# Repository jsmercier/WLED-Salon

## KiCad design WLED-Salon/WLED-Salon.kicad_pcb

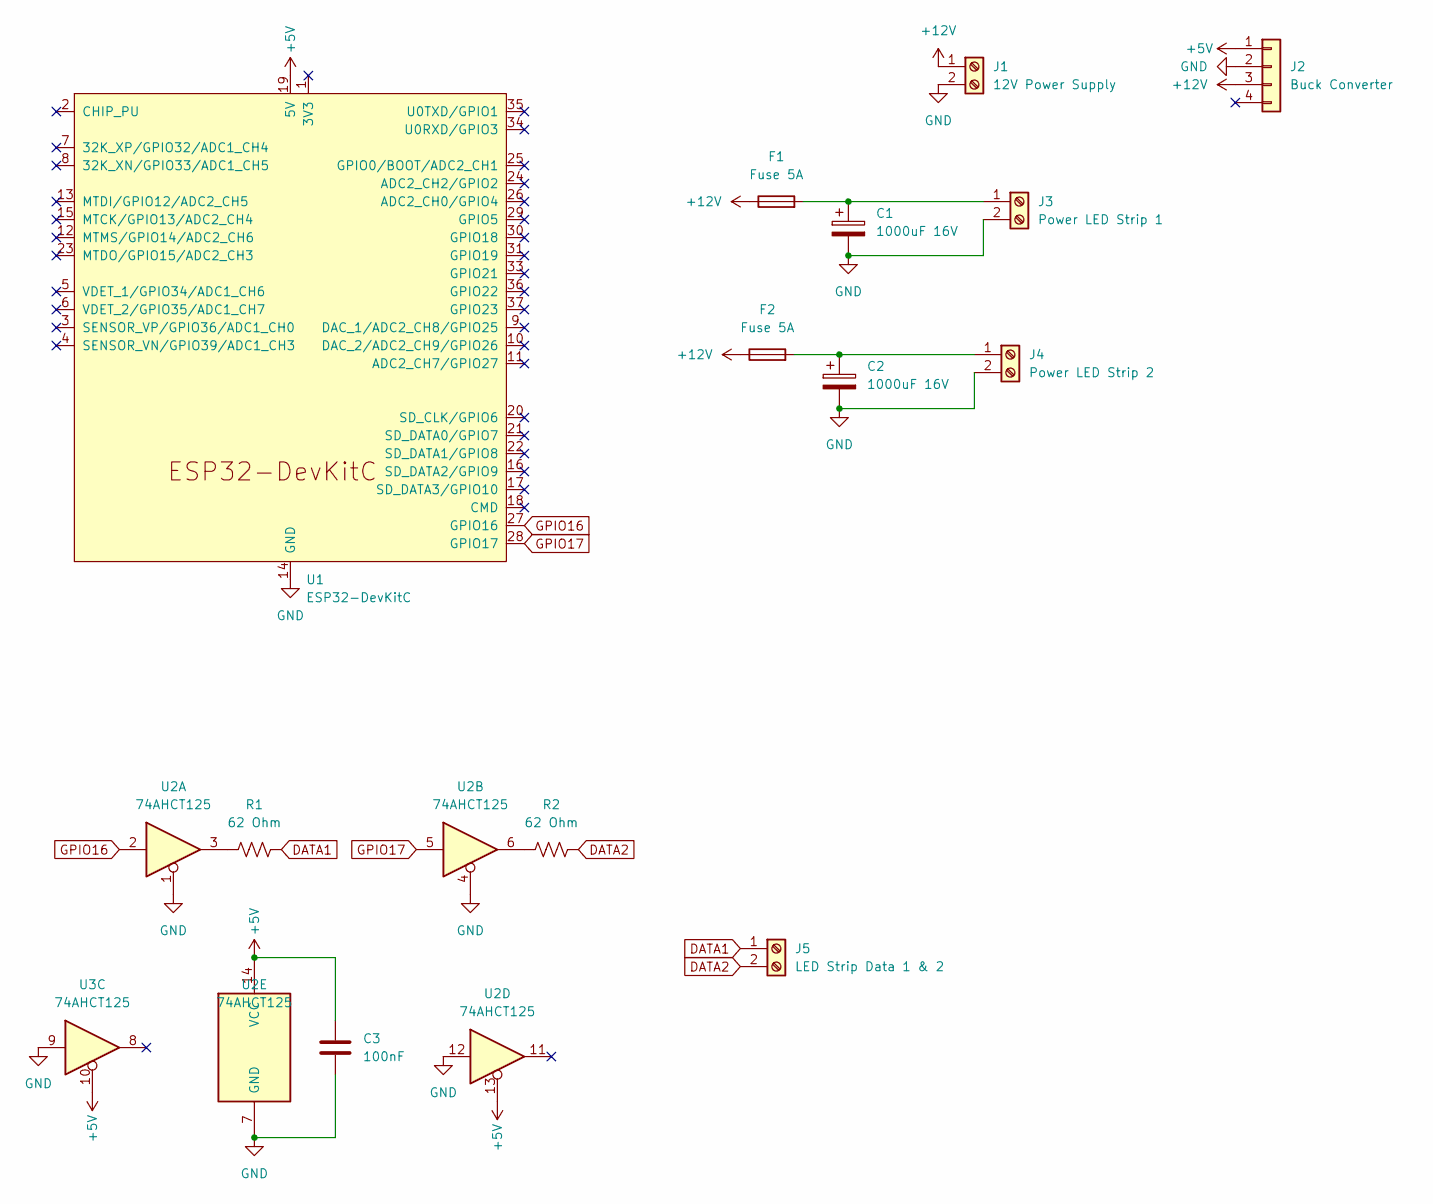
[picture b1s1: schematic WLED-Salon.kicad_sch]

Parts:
C1, C2: 1000uF 16V
C3: 100nF
F1, F2: Fuse 5A
J1: 12V Power Supply
J2: Buck Converter
J3: Power LED Strip 1
J4: Power LED Strip 2
J5: LED Strip Data 1 & 2
R1, R2: 62 Ohm
U1: ESP32-DevKitC
U2, U3: 74AHCT125; DIP-14_W7.62mm_Socket

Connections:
+5V: C3.1, J2.1, U1.19 (5V), U2.10, U2.13, U2.14 (VCC), U3.10
+12V: F1.1, F2.1, J1.1, J2.3
DATA1: J5.1, R1.2
DATA2: J5.2, R2.2
GND: C1.2, C2.2, C3.2, J1.2, J2.2, J3.2, J4.2, U1.14 (GND), U1.32 (GND), U1.38 (GND), U2.1, U2.4, U2.7 (GND), U2.9, U2.12, U3.9
GPIO16: U1.27 (GPIO16), U2.2
GPIO17: U1.28 (GPIO17), U2.5
unnamed: C1.1, F1.2, J3.1
unnamed: C2.1, F2.2, J4.1
unnamed: R1.1, U2.3
unnamed: R2.1, U2.6

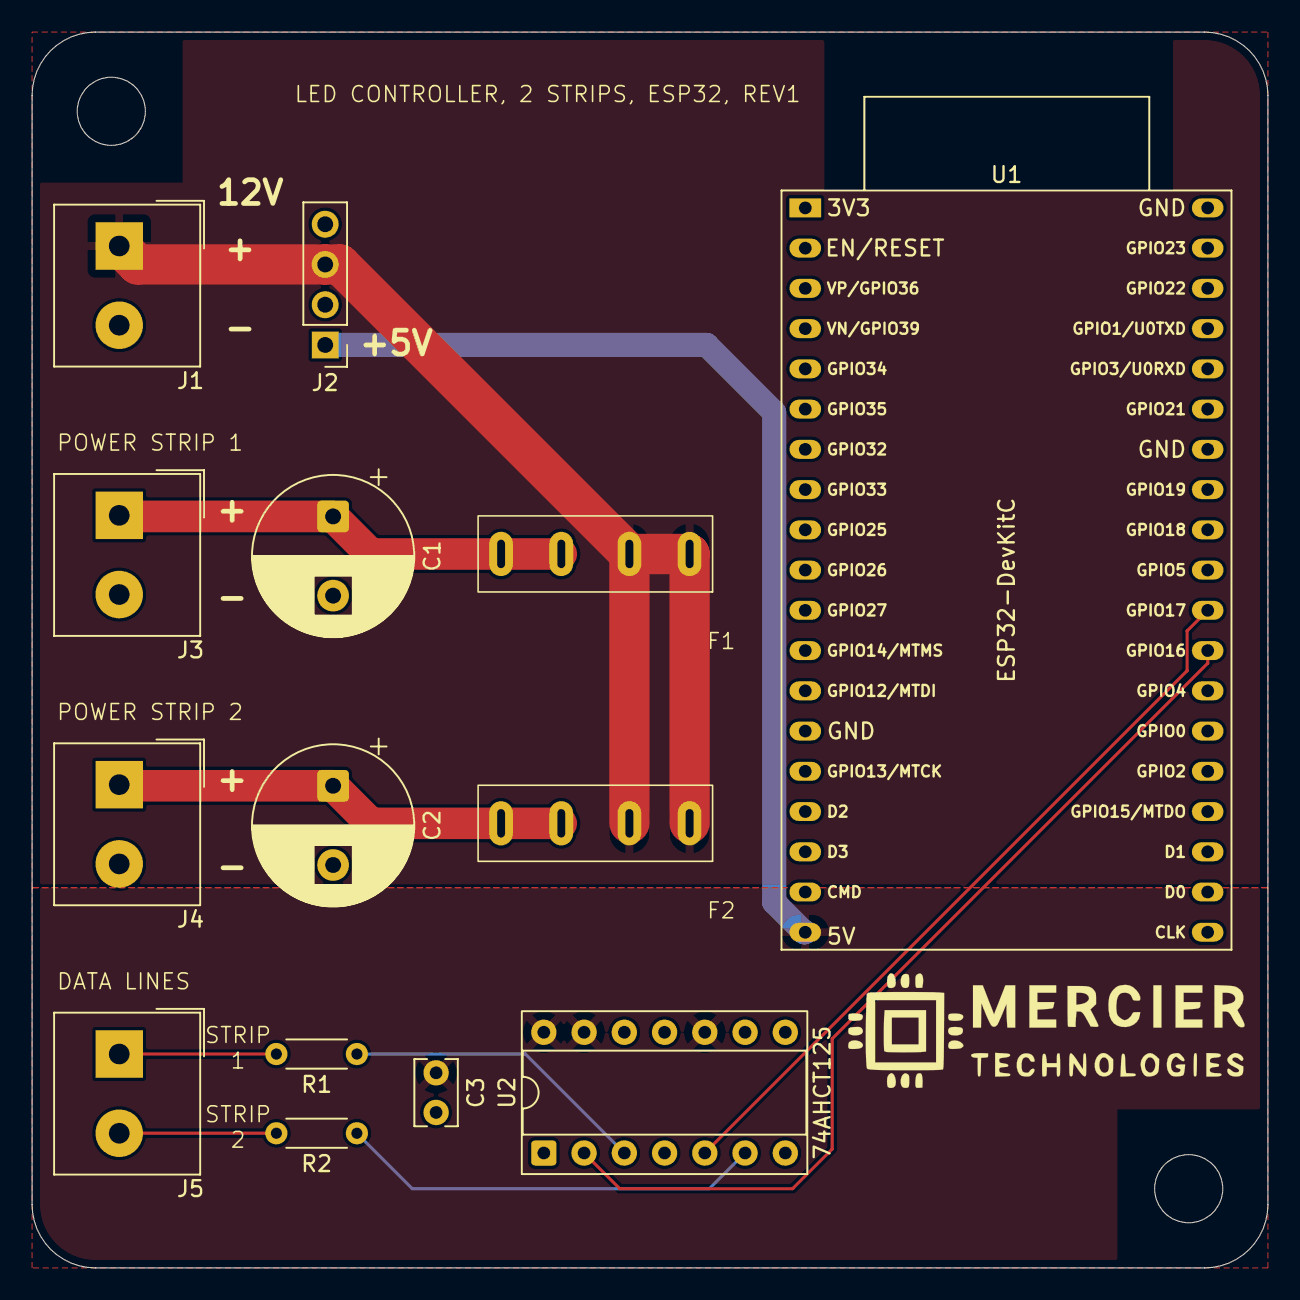
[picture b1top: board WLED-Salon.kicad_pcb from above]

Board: 2 copper layers, 78.0 x 78.0 mm, 14 parts (0 on the bottom side), 11 nets.

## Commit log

2025-05-10 added some kicad lib, logo and digikey
2025-05-10 moved folder
2025-05-11 kicad proj started, esp lib
2025-05-16 schematic advancements
2025-05-19 pcs done mostly
2025-05-19 pcb ordered
2025-05-20 added drill files to gerber files
2025-05-23 autosave
